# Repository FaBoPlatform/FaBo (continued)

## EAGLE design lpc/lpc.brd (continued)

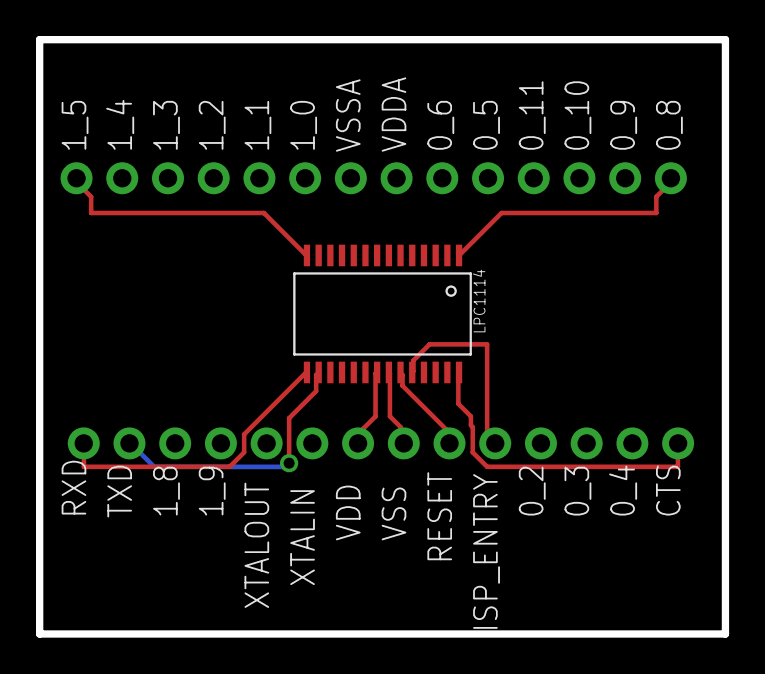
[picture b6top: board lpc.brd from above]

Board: 2 copper layers, 38.1 x 33.0 mm, 3 parts (0 on the bottom side), 9 nets.
